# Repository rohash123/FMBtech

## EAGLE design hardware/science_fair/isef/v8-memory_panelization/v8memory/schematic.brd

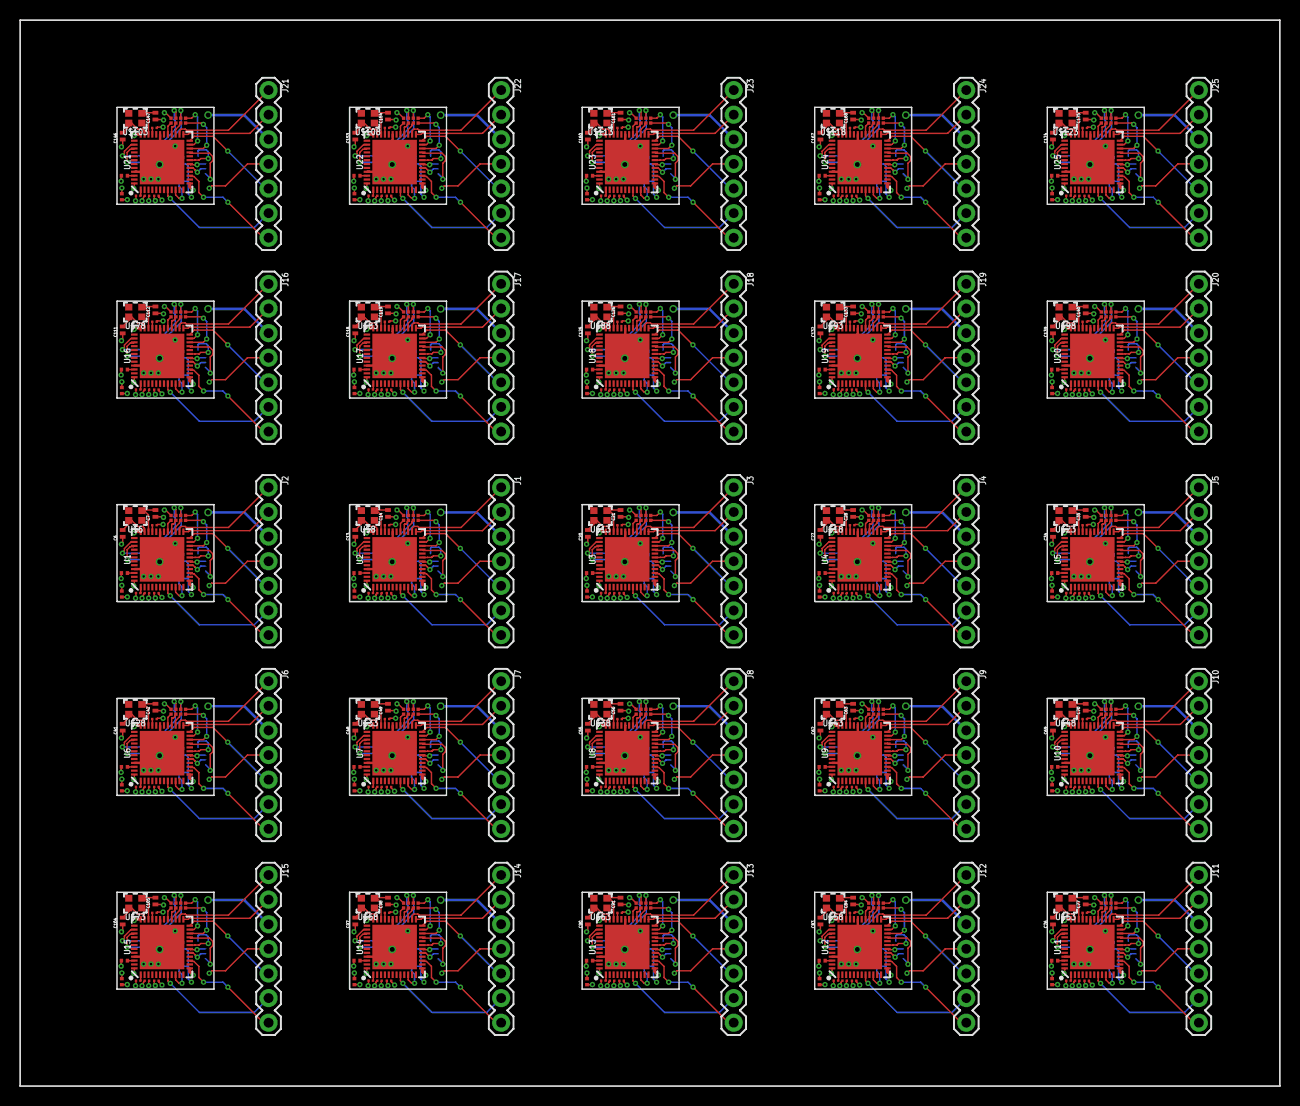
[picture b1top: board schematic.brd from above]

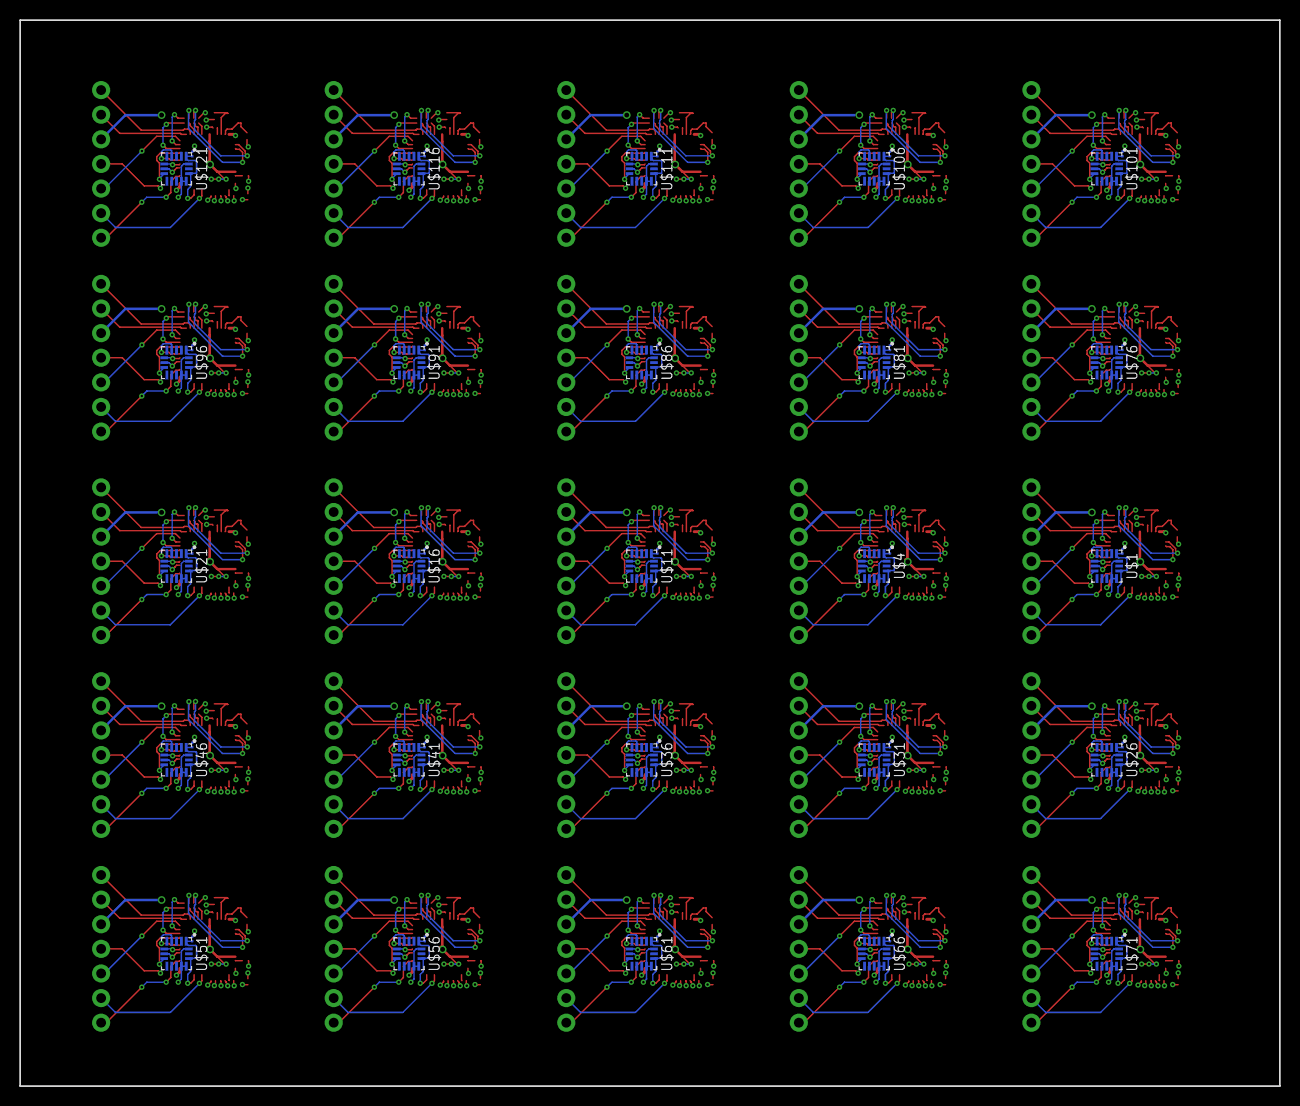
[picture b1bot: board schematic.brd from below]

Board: 4 copper layers, 130.0 x 110.0 mm, 350 parts (50 on the bottom side), 600 nets.

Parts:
C1, C2, C3, C4, C8, C9, C10, C11, C15, C16, C17, C18, C22, C23, C24, C25, C29, C30, C31, C32, C36, C37, C38, C39, C43, C44, C45, C46, C50, C51, C52, C53, C57, C58, C59, C60, C64, C65, C66, C67, C71, C72, C73, C74, C78, C79, C80, C81, C85, C86, C87, C88, C92, C93, C94, C95, C99, C100, C101, C102, C106, C107, C108, C109, C113, C114, C115, C116, C120, C121, C122, C123, C127, C128, C129, C130, C134, C135, C136, C137, C141, C142, C143, C144, C148, C149, C150, C151, C155, C156, C157, C158, C162, C163, C164, C165, C169, C170, C171, C172: C0402X5R0G104M020BCCAP_0402-L; CAP_0402-L
C5, C12, C19, C26, C33, C40, C47, C54, C61, C68, C75, C82, C89, C96, C103, C110, C117, C124, C131, C138, C145, C152, C159, C166, C173: C0402C0G1C101J020BCCAP_0402-L; CAP_0402-L
C6, C7, C13, C14, C20, C21, C27, C28, C34, C35, C41, C42, C48, C49, C55, C56, C62, C63, C69, C70, C76, C77, C83, C84, C90, C91, C97, C98, C104, C105, C111, C112, C118, C119, C125, C126, C132, C133, C139, C140, C146, C147, C153, C154, C160, C161, C167, C168, C174, C175: GRM1555C1H6R0CA01D; CAPC1005X55N
J1, J2, J3, J4, J5, J6, J7, J8, J9, J10, J11, J12, J13, J14, J15, J16, J17, J18, J19, J20, J21, J22, J23, J24, J25: header; 1X07
U1, U2, U3, U4, U5, U6, U7, U8, U9, U10, U11, U12, U13, U14, U15, U16, U17, U18, U19, U20, U21, U22, U23, U24, U25: NRF52832; QFN48-6X6MM
U$1, U$4, U$11, U$16, U$21, U$26, U$31, U$36, U$41, U$46, U$51, U$56, U$61, U$66, U$71, U$76, U$81, U$86, U$91, U$96, U$101, U$106, U$111, U$116, U$121: ADXL362; TFLGA-16/3.3MMX3.1MM
U$2, U$5, U$12, U$17, U$22, U$27, U$32, U$37, U$42, U$47, U$52, U$57, U$62, U$67, U$72, U$77, U$82, U$87, U$92, U$97, U$102, U$107, U$112, U$117, U$122: 4P7UFCAPACITOR
U$3, U$10, U$15, U$20, U$25, U$30, U$35, U$40, U$45, U$50, U$55, U$60, U$65, U$70, U$75, U$80, U$85, U$90, U$95, U$100, U$105, U$110, U$115, U$120, U$125: AT25SF161-UUD-T
U$6, U$8, U$13, U$18, U$23, U$28, U$33, U$38, U$43, U$48, U$53, U$58, U$63, U$68, U$73, U$78, U$83, U$88, U$93, U$98, U$103, U$108, U$113, U$118, U$123: 32MHZCRYSTAL
U$7, U$9, U$14, U$19, U$24, U$29, U$34, U$39, U$44, U$49, U$54, U$59, U$64, U$69, U$74, U$79, U$84, U$89, U$94, U$99, U$104, U$109, U$114, U$119, U$124: 1UFCAPACITOR

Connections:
ADXL_POWER-QFAA: C1.2, U1.10, U$1.VDD/IO, U$1.VS
ADXL_POWER-QFAA1: C8.2, U2.10, U$4.VDD/IO, U$4.VS
ADXL_POWER-QFAA2: C15.2, U3.10, U$11.VDD/IO, U$11.VS
ADXL_POWER-QFAA3: C22.2, U4.10, U$16.VDD/IO, U$16.VS
ADXL_POWER-QFAA4: C29.2, U5.10, U$21.VDD/IO, U$21.VS
ADXL_POWER-QFAA5: C36.2, U6.10, U$26.VDD/IO, U$26.VS
ADXL_POWER-QFAA6: C43.2, U7.10, U$31.VDD/IO, U$31.VS
ADXL_POWER-QFAA7: C50.2, U8.10, U$36.VDD/IO, U$36.VS
ADXL_POWER-QFAA8: C57.2, U9.10, U$41.VDD/IO, U$41.VS
ADXL_POWER-QFAA9: C64.2, U10.10, U$46.VDD/IO, U$46.VS
ADXL_POWER-QFAA10: C71.2, U11.10, U$51.VDD/IO, U$51.VS
ADXL_POWER-QFAA11: C78.2, U12.10, U$56.VDD/IO, U$56.VS
ADXL_POWER-QFAA12: C85.2, U13.10, U$61.VDD/IO, U$61.VS
ADXL_POWER-QFAA13: C92.2, U14.10, U$66.VDD/IO, U$66.VS
ADXL_POWER-QFAA14: C99.2, U15.10, U$71.VDD/IO, U$71.VS
ADXL_POWER-QFAA15: C106.2, U16.10, U$76.VDD/IO, U$76.VS
ADXL_POWER-QFAA16: C113.2, U17.10, U$81.VDD/IO, U$81.VS
ADXL_POWER-QFAA17: C120.2, U18.10, U$86.VDD/IO, U$86.VS
ADXL_POWER-QFAA18: C127.2, U19.10, U$91.VDD/IO, U$91.VS
ADXL_POWER-QFAA19: C134.2, U20.10, U$96.VDD/IO, U$96.VS
ADXL_POWER-QFAA20: C141.2, U21.10, U$101.VDD/IO, U$101.VS
ADXL_POWER-QFAA21: C148.2, U22.10, U$106.VDD/IO, U$106.VS
ADXL_POWER-QFAA22: C155.2, U23.10, U$111.VDD/IO, U$111.VS
ADXL_POWER-QFAA23: C162.2, U24.10, U$116.VDD/IO, U$116.VS
ADXL_POWER-QFAA24: C169.2, U25.10, U$121.VDD/IO, U$121.VS
CS-QFAA: U1.21, U$1.CS
CS-QFAA1: U2.21, U$4.CS
CS-QFAA2: U3.21, U$11.CS
CS-QFAA3: U4.21, U$16.CS
CS-QFAA4: U5.21, U$21.CS
CS-QFAA5: U6.21, U$26.CS
CS-QFAA6: U7.21, U$31.CS
CS-QFAA7: U8.21, U$36.CS
CS-QFAA8: U9.21, U$41.CS
CS-QFAA9: U10.21, U$46.CS
CS-QFAA10: U11.21, U$51.CS
CS-QFAA11: U12.21, U$56.CS
CS-QFAA12: U13.21, U$61.CS
CS-QFAA13: U14.21, U$66.CS
CS-QFAA14: U15.21, U$71.CS
CS-QFAA15: U16.21, U$76.CS
CS-QFAA16: U17.21, U$81.CS
CS-QFAA17: U18.21, U$86.CS
CS-QFAA18: U19.21, U$91.CS
CS-QFAA19: U20.21, U$96.CS
CS-QFAA20: U21.21, U$101.CS
CS-QFAA21: U22.21, U$106.CS
CS-QFAA22: U23.21, U$111.CS
CS-QFAA23: U24.21, U$116.CS
CS-QFAA24: U25.21, U$121.CS
CS_FLASH: U1.23, U$3.5
CS_FLASH1: U2.23, U$10.5
CS_FLASH2: U3.23, U$15.5
CS_FLASH3: U4.23, U$20.5
CS_FLASH4: U5.23, U$25.5
CS_FLASH5: U6.23, U$30.5
CS_FLASH6: U7.23, U$35.5
CS_FLASH7: U8.23, U$40.5
CS_FLASH8: U9.23, U$45.5
CS_FLASH9: U10.23, U$50.5
CS_FLASH10: U11.23, U$55.5
CS_FLASH11: U12.23, U$60.5
CS_FLASH12: U13.23, U$65.5
CS_FLASH13: U14.23, U$70.5
CS_FLASH14: U15.23, U$75.5
CS_FLASH15: U16.23, U$80.5
CS_FLASH16: U17.23, U$85.5
CS_FLASH17: U18.23, U$90.5
CS_FLASH18: U19.23, U$95.5
CS_FLASH19: U20.23, U$100.5
CS_FLASH20: U21.23, U$105.5
CS_FLASH21: U22.23, U$110.5
CS_FLASH22: U23.23, U$115.5
CS_FLASH23: U24.23, U$120.5
CS_FLASH24: U25.23, U$125.5
DEC1-QFAA: C2.1, U1.1
DEC1-QFAA1: C9.1, U2.1
DEC1-QFAA2: C16.1, U3.1
DEC1-QFAA3: C23.1, U4.1
DEC1-QFAA4: C30.1, U5.1
DEC1-QFAA5: C37.1, U6.1
DEC1-QFAA6: C44.1, U7.1
DEC1-QFAA7: C51.1, U8.1
DEC1-QFAA8: C58.1, U9.1
DEC1-QFAA9: C65.1, U10.1
DEC1-QFAA10: C72.1, U11.1
DEC1-QFAA11: C79.1, U12.1
DEC1-QFAA12: C86.1, U13.1
DEC1-QFAA13: C93.1, U14.1
DEC1-QFAA14: C100.1, U15.1
DEC1-QFAA15: C107.1, U16.1
DEC1-QFAA16: C114.1, U17.1
DEC1-QFAA17: C121.1, U18.1
DEC1-QFAA18: C128.1, U19.1
DEC1-QFAA19: C135.1, U20.1
DEC1-QFAA20: C142.1, U21.1
DEC1-QFAA21: C149.1, U22.1
DEC1-QFAA22: C156.1, U23.1
DEC1-QFAA23: C163.1, U24.1
DEC1-QFAA24: C170.1, U25.1
DEC3-QFAA: C5.1, U1.33
DEC3-QFAA1: C12.1, U2.33
DEC3-QFAA2: C19.1, U3.33
DEC3-QFAA3: C26.1, U4.33
DEC3-QFAA4: C33.1, U5.33
DEC3-QFAA5: C40.1, U6.33
DEC3-QFAA6: C47.1, U7.33
DEC3-QFAA7: C54.1, U8.33
DEC3-QFAA8: C61.1, U9.33
DEC3-QFAA9: C68.1, U10.33
DEC3-QFAA10: C75.1, U11.33
DEC3-QFAA11: C82.1, U12.33
DEC3-QFAA12: C89.1, U13.33
DEC3-QFAA13: C96.1, U14.33
DEC3-QFAA14: C103.1, U15.33
DEC3-QFAA15: C110.1, U16.33
DEC3-QFAA16: C117.1, U17.33
DEC3-QFAA17: C124.1, U18.33
DEC3-QFAA18: C131.1, U19.33
DEC3-QFAA19: C138.1, U20.33
DEC3-QFAA20: C145.1, U21.33
DEC3-QFAA21: C152.1, U22.33
DEC3-QFAA22: C159.1, U23.33
DEC3-QFAA23: C166.1, U24.33
DEC3-QFAA24: C173.1, U25.33
DEC4-QFAA: U1.46, U$7.P$4
DEC4-QFAA1: U2.46, U$9.P$4
DEC4-QFAA2: U3.46, U$14.P$4
DEC4-QFAA3: U4.46, U$19.P$4
DEC4-QFAA4: U5.46, U$24.P$4
DEC4-QFAA5: U6.46, U$29.P$4
DEC4-QFAA6: U7.46, U$34.P$4
DEC4-QFAA7: U8.46, U$39.P$4
DEC4-QFAA8: U9.46, U$44.P$4
DEC4-QFAA9: U10.46, U$49.P$4
DEC4-QFAA10: U11.46, U$54.P$4
DEC4-QFAA11: U12.46, U$59.P$4
DEC4-QFAA12: U13.46, U$64.P$4
DEC4-QFAA13: U14.46, U$69.P$4
DEC4-QFAA14: U15.46, U$74.P$4
DEC4-QFAA15: U16.46, U$79.P$4
DEC4-QFAA16: U17.46, U$84.P$4
DEC4-QFAA17: U18.46, U$89.P$4
DEC4-QFAA18: U19.46, U$94.P$4
DEC4-QFAA19: U20.46, U$99.P$4
DEC4-QFAA20: U21.46, U$104.P$4
DEC4-QFAA21: U22.46, U$109.P$4
DEC4-QFAA22: U23.46, U$114.P$4
DEC4-QFAA23: U24.46, U$119.P$4
DEC4-QFAA24: U25.46, U$124.P$4
FLASH_POWER: U1.22, U$3.1
FLASH_POWER1: U2.22, U$10.1
FLASH_POWER2: U3.22, U$15.1
FLASH_POWER3: U4.22, U$20.1
FLASH_POWER4: U5.22, U$25.1
FLASH_POWER5: U6.22, U$30.1
FLASH_POWER6: U7.22, U$35.1
FLASH_POWER7: U8.22, U$40.1
FLASH_POWER8: U9.22, U$45.1
FLASH_POWER9: U10.22, U$50.1
FLASH_POWER10: U11.22, U$55.1
FLASH_POWER11: U12.22, U$60.1
FLASH_POWER12: U13.22, U$65.1
FLASH_POWER13: U14.22, U$70.1
FLASH_POWER14: U15.22, U$75.1
FLASH_POWER15: U16.22, U$80.1
FLASH_POWER16: U17.22, U$85.1
FLASH_POWER17: U18.22, U$90.1
FLASH_POWER18: U19.22, U$95.1
FLASH_POWER19: U20.22, U$100.1
FLASH_POWER20: U21.22, U$105.1
FLASH_POWER21: U22.22, U$110.1
FLASH_POWER22: U23.22, U$115.1
FLASH_POWER23: U24.22, U$120.1
FLASH_POWER24: U25.22, U$125.1
GND: C1.1, C2.2, C3.1, C4.1, C5.2, C6.1, C7.1, J2.4, U1.31, U1.45, U1.EP, U$1.GND@1, U$1.GND@2, U$1.GND@3, U$2.P$4, U$3.8, U$7.P$3
GND1: C8.1, C9.2, C10.1, C11.1, C12.2, C13.1, C14.1, J1.4, U2.31, U2.45, U2.EP, U$4.GND@1, U$4.GND@2, U$4.GND@3, U$5.P$4, U$9.P$3, U$10.8
GND2: C15.1, C16.2, C17.1, C18.1, C19.2, C20.1, C21.1, J3.4, U3.31, U3.45, U3.EP, U$11.GND@1, U$11.GND@2, U$11.GND@3, U$12.P$4, U$14.P$3, U$15.8
GND3: C22.1, C23.2, C24.1, C25.1, C26.2, C27.1, C28.1, J4.4, U4.31, U4.45, U4.EP, U$16.GND@1, U$16.GND@2, U$16.GND@3, U$17.P$4, U$19.P$3, U$20.8
GND4: C29.1, C30.2, C31.1, C32.1, C33.2, C34.1, C35.1, J5.4, U5.31, U5.45, U5.EP, U$21.GND@1, U$21.GND@2, U$21.GND@3, U$22.P$4, U$24.P$3, U$25.8
GND5: C36.1, C37.2, C38.1, C39.1, C40.2, C41.1, C42.1, J6.4, U6.31, U6.45, U6.EP, U$26.GND@1, U$26.GND@2, U$26.GND@3, U$27.P$4, U$29.P$3, U$30.8
GND6: C43.1, C44.2, C45.1, C46.1, C47.2, C48.1, C49.1, J7.4, U7.31, U7.45, U7.EP, U$31.GND@1, U$31.GND@2, U$31.GND@3, U$32.P$4, U$34.P$3, U$35.8
GND7: C50.1, C51.2, C52.1, C53.1, C54.2, C55.1, C56.1, J8.4, U8.31, U8.45, U8.EP, U$36.GND@1, U$36.GND@2, U$36.GND@3, U$37.P$4, U$39.P$3, U$40.8
GND8: C57.1, C58.2, C59.1, C60.1, C61.2, C62.1, C63.1, J9.4, U9.31, U9.45, U9.EP, U$41.GND@1, U$41.GND@2, U$41.GND@3, U$42.P$4, U$44.P$3, U$45.8
GND9: C64.1, C65.2, C66.1, C67.1, C68.2, C69.1, C70.1, J10.4, U10.31, U10.45, U10.EP, U$46.GND@1, U$46.GND@2, U$46.GND@3, U$47.P$4, U$49.P$3, U$50.8
GND10: C71.1, C72.2, C73.1, C74.1, C75.2, C76.1, C77.1, J11.4, U11.31, U11.45, U11.EP, U$51.GND@1, U$51.GND@2, U$51.GND@3, U$52.P$4, U$54.P$3, U$55.8
GND11: C78.1, C79.2, C80.1, C81.1, C82.2, C83.1, C84.1, J12.4, U12.31, U12.45, U12.EP, U$56.GND@1, U$56.GND@2, U$56.GND@3, U$57.P$4, U$59.P$3, U$60.8
GND12: C85.1, C86.2, C87.1, C88.1, C89.2, C90.1, C91.1, J13.4, U13.31, U13.45, U13.EP, U$61.GND@1, U$61.GND@2, U$61.GND@3, U$62.P$4, U$64.P$3, U$65.8
GND13: C92.1, C93.2, C94.1, C95.1, C96.2, C97.1, C98.1, J14.4, U14.31, U14.45, U14.EP, U$66.GND@1, U$66.GND@2, U$66.GND@3, U$67.P$4, U$69.P$3, U$70.8
GND14: C99.1, C100.2, C101.1, C102.1, C103.2, C104.1, C105.1, J15.4, U15.31, U15.45, U15.EP, U$71.GND@1, U$71.GND@2, U$71.GND@3, U$72.P$4, U$74.P$3, U$75.8
GND15: C106.1, C107.2, C108.1, C109.1, C110.2, C111.1, C112.1, J16.4, U16.31, U16.45, U16.EP, U$76.GND@1, U$76.GND@2, U$76.GND@3, U$77.P$4, U$79.P$3, U$80.8
GND16: C113.1, C114.2, C115.1, C116.1, C117.2, C118.1, C119.1, J17.4, U17.31, U17.45, U17.EP, U$81.GND@1, U$81.GND@2, U$81.GND@3, U$82.P$4, U$84.P$3, U$85.8
GND17: C120.1, C121.2, C122.1, C123.1, C124.2, C125.1, C126.1, J18.4, U18.31, U18.45, U18.EP, U$86.GND@1, U$86.GND@2, U$86.GND@3, U$87.P$4, U$89.P$3, U$90.8
GND18: C127.1, C128.2, C129.1, C130.1, C131.2, C132.1, C133.1, J19.4, U19.31, U19.45, U19.EP, U$91.GND@1, U$91.GND@2, U$91.GND@3, U$92.P$4, U$94.P$3, U$95.8
GND19: C134.1, C135.2, C136.1, C137.1, C138.2, C139.1, C140.1, J20.4, U20.31, U20.45, U20.EP, U$96.GND@1, U$96.GND@2, U$96.GND@3, U$97.P$4, U$99.P$3, U$100.8
GND20: C141.1, C142.2, C143.1, C144.1, C145.2, C146.1, C147.1, J21.4, U21.31, U21.45, U21.EP, U$101.GND@1, U$101.GND@2, U$101.GND@3, U$102.P$4, U$104.P$3, U$105.8
GND21: C148.1, C149.2, C150.1, C151.1, C152.2, C153.1, C154.1, J22.4, U22.31, U22.45, U22.EP, U$106.GND@1, U$106.GND@2, U$106.GND@3, U$107.P$4, U$109.P$3, U$110.8
GND22: C155.1, C156.2, C157.1, C158.1, C159.2, C160.1, C161.1, J23.4, U23.31, U23.45, U23.EP, U$111.GND@1, U$111.GND@2, U$111.GND@3, U$112.P$4, U$114.P$3, U$115.8
GND23: C162.1, C163.2, C164.1, C165.1, C166.2, C167.1, C168.1, J24.4, U24.31, U24.45, U24.EP, U$116.GND@1, U$116.GND@2, U$116.GND@3, U$117.P$4, U$119.P$3, U$120.8
GND24: C169.1, C170.2, C171.1, C172.1, C173.2, C174.1, C175.1, J25.4, U25.31, U25.45, U25.EP, U$121.GND@1, U$121.GND@2, U$121.GND@3, U$122.P$4, U$124.P$3, U$125.8
HOLD_FLASH: U1.27, U$3.2
HOLD_FLASH1: U2.27, U$10.2
HOLD_FLASH2: U3.27, U$15.2
HOLD_FLASH3: U4.27, U$20.2
HOLD_FLASH4: U5.27, U$25.2
HOLD_FLASH5: U6.27, U$30.2
HOLD_FLASH6: U7.27, U$35.2
HOLD_FLASH7: U8.27, U$40.2
HOLD_FLASH8: U9.27, U$45.2
HOLD_FLASH9: U10.27, U$50.2
HOLD_FLASH10: U11.27, U$55.2
HOLD_FLASH11: U12.27, U$60.2
HOLD_FLASH12: U13.27, U$65.2
HOLD_FLASH13: U14.27, U$70.2
HOLD_FLASH14: U15.27, U$75.2
HOLD_FLASH15: U16.27, U$80.2
HOLD_FLASH16: U17.27, U$85.2
HOLD_FLASH17: U18.27, U$90.2
HOLD_FLASH18: U19.27, U$95.2
HOLD_FLASH19: U20.27, U$100.2
HOLD_FLASH20: U21.27, U$105.2
HOLD_FLASH21: U22.27, U$110.2
HOLD_FLASH22: U23.27, U$115.2
HOLD_FLASH23: U24.27, U$120.2
HOLD_FLASH24: U25.27, U$125.2
MISO-QFAA: U1.17, U$1.MISO
MISO-QFAA1: U2.17, U$4.MISO
MISO-QFAA2: U3.17, U$11.MISO
MISO-QFAA3: U4.17, U$16.MISO
MISO-QFAA4: U5.17, U$21.MISO
MISO-QFAA5: U6.17, U$26.MISO
MISO-QFAA6: U7.17, U$31.MISO
MISO-QFAA7: U8.17, U$36.MISO
MISO-QFAA8: U9.17, U$41.MISO
MISO-QFAA9: U10.17, U$46.MISO
MISO-QFAA10: U11.17, U$51.MISO
MISO-QFAA11: U12.17, U$56.MISO
MISO-QFAA12: U13.17, U$61.MISO
MISO-QFAA13: U14.17, U$66.MISO
MISO-QFAA14: U15.17, U$71.MISO
MISO-QFAA15: U16.17, U$76.MISO
MISO-QFAA16: U17.17, U$81.MISO
MISO-QFAA17: U18.17, U$86.MISO
MISO-QFAA18: U19.17, U$91.MISO
MISO-QFAA19: U20.17, U$96.MISO
MISO-QFAA20: U21.17, U$101.MISO
MISO-QFAA21: U22.17, U$106.MISO
MISO-QFAA22: U23.17, U$111.MISO
MISO-QFAA23: U24.17, U$116.MISO
MISO-QFAA24: U25.17, U$121.MISO
MOSI-QFAA: U1.18, U$1.MOSI
MOSI-QFAA1: U2.18, U$4.MOSI
MOSI-QFAA2: U3.18, U$11.MOSI
MOSI-QFAA3: U4.18, U$16.MOSI
MOSI-QFAA4: U5.18, U$21.MOSI
MOSI-QFAA5: U6.18, U$26.MOSI
MOSI-QFAA6: U7.18, U$31.MOSI
MOSI-QFAA7: U8.18, U$36.MOSI
MOSI-QFAA8: U9.18, U$41.MOSI
MOSI-QFAA9: U10.18, U$46.MOSI
MOSI-QFAA10: U11.18, U$51.MOSI
MOSI-QFAA11: U12.18, U$56.MOSI
MOSI-QFAA12: U13.18, U$61.MOSI
MOSI-QFAA13: U14.18, U$66.MOSI
MOSI-QFAA14: U15.18, U$71.MOSI
MOSI-QFAA15: U16.18, U$76.MOSI
MOSI-QFAA16: U17.18, U$81.MOSI
MOSI-QFAA17: U18.18, U$86.MOSI
MOSI-QFAA18: U19.18, U$91.MOSI
MOSI-QFAA19: U20.18, U$96.MOSI
MOSI-QFAA20: U21.18, U$101.MOSI
MOSI-QFAA21: U22.18, U$106.MOSI
MOSI-QFAA22: U23.18, U$111.MOSI
MOSI-QFAA23: U24.18, U$116.MOSI
MOSI-QFAA24: U25.18, U$121.MOSI
P0.06-QFAA: J2.6, U1.8
P0.06-QFAA1: J1.6, U2.8
P0.06-QFAA2: J3.6, U3.8
P0.06-QFAA3: J4.6, U4.8
P0.06-QFAA4: J5.6, U5.8
P0.06-QFAA5: J6.6, U6.8
P0.06-QFAA6: J7.6, U7.8
P0.06-QFAA7: J8.6, U8.8
P0.06-QFAA8: J9.6, U9.8
P0.06-QFAA9: J10.6, U10.8
P0.06-QFAA10: J11.6, U11.8
P0.06-QFAA11: J12.6, U12.8
P0.06-QFAA12: J13.6, U13.8
P0.06-QFAA13: J14.6, U14.8
P0.06-QFAA14: J15.6, U15.8
P0.06-QFAA15: J16.6, U16.8
P0.06-QFAA16: J17.6, U17.8
P0.06-QFAA17: J18.6, U18.8
P0.06-QFAA18: J19.6, U19.8
P0.06-QFAA19: J20.6, U20.8
P0.06-QFAA20: J21.6, U21.8
P0.06-QFAA21: J22.6, U22.8
P0.06-QFAA22: J23.6, U23.8
P0.06-QFAA23: J24.6, U24.8
P0.06-QFAA24: J25.6, U25.8
P0.12-QFAA: J2.7, U1.15
P0.12-QFAA1: J1.7, U2.15
P0.12-QFAA2: J3.7, U3.15
P0.12-QFAA3: J4.7, U4.15
P0.12-QFAA4: J5.7, U5.15
P0.12-QFAA5: J6.7, U6.15
P0.12-QFAA6: J7.7, U7.15
P0.12-QFAA7: J8.7, U8.15
P0.12-QFAA8: J9.7, U9.15
P0.12-QFAA9: J10.7, U10.15
P0.12-QFAA10: J11.7, U11.15
P0.12-QFAA11: J12.7, U12.15
P0.12-QFAA12: J13.7, U13.15
P0.12-QFAA13: J14.7, U14.15
P0.12-QFAA14: J15.7, U15.15
P0.12-QFAA15: J16.7, U16.15
P0.12-QFAA16: J17.7, U17.15
P0.12-QFAA17: J18.7, U18.15
P0.12-QFAA18: J19.7, U19.15
P0.12-QFAA19: J20.7, U20.15
P0.12-QFAA20: J21.7, U21.15
P0.12-QFAA21: J22.7, U22.15
P0.12-QFAA22: J23.7, U23.15
P0.12-QFAA23: J24.7, U24.15
P0.12-QFAA24: J25.7, U25.15
RESET-QFAA: J2.5, U1.24
RESET-QFAA1: J1.5, U2.24
RESET-QFAA2: J3.5, U3.24
RESET-QFAA3: J4.5, U4.24
RESET-QFAA4: J5.5, U5.24
RESET-QFAA5: J6.5, U6.24
RESET-QFAA6: J7.5, U7.24
RESET-QFAA7: J8.5, U8.24
RESET-QFAA8: J9.5, U9.24
RESET-QFAA9: J10.5, U10.24
RESET-QFAA10: J11.5, U11.24
RESET-QFAA11: J12.5, U12.24
RESET-QFAA12: J13.5, U13.24
RESET-QFAA13: J14.5, U14.24
RESET-QFAA14: J15.5, U15.24
RESET-QFAA15: J16.5, U16.24
RESET-QFAA16: J17.5, U17.24
RESET-QFAA17: J18.5, U18.24
RESET-QFAA18: J19.5, U19.24
RESET-QFAA19: J20.5, U20.24
RESET-QFAA20: J21.5, U21.24
RESET-QFAA21: J22.5, U22.24
RESET-QFAA22: J23.5, U23.24
RESET-QFAA23: J24.5, U24.24
RESET-QFAA24: J25.5, U25.24
SCK_FLASH: U1.28, U$3.3
SCK_FLASH1: U2.28, U$10.3
SCK_FLASH2: U3.28, U$15.3
SCK_FLASH3: U4.28, U$20.3
SCK_FLASH4: U5.28, U$25.3
SCK_FLASH5: U6.28, U$30.3
SCK_FLASH6: U7.28, U$35.3
SCK_FLASH7: U8.28, U$40.3
SCK_FLASH8: U9.28, U$45.3
SCK_FLASH9: U10.28, U$50.3
SCK_FLASH10: U11.28, U$55.3
SCK_FLASH11: U12.28, U$60.3
SCK_FLASH12: U13.28, U$65.3
SCK_FLASH13: U14.28, U$70.3
SCK_FLASH14: U15.28, U$75.3
SCK_FLASH15: U16.28, U$80.3
SCK_FLASH16: U17.28, U$85.3
SCK_FLASH17: U18.28, U$90.3
SCK_FLASH18: U19.28, U$95.3
SCK_FLASH19: U20.28, U$100.3
SCK_FLASH20: U21.28, U$105.3
SCK_FLASH21: U22.28, U$110.3
SCK_FLASH22: U23.28, U$115.3
SCK_FLASH23: U24.28, U$120.3
SCK_FLASH24: U25.28, U$125.3
SCLK-QFAA: U1.19, U$1.SCLK
SCLK-QFAA1: U2.19, U$4.SCLK
SCLK-QFAA2: U3.19, U$11.SCLK
SCLK-QFAA3: U4.19, U$16.SCLK
SCLK-QFAA4: U5.19, U$21.SCLK
SCLK-QFAA5: U6.19, U$26.SCLK
SCLK-QFAA6: U7.19, U$31.SCLK
SCLK-QFAA7: U8.19, U$36.SCLK
SCLK-QFAA8: U9.19, U$41.SCLK
SCLK-QFAA9: U10.19, U$46.SCLK
SCLK-QFAA10: U11.19, U$51.SCLK
SCLK-QFAA11: U12.19, U$56.SCLK
SCLK-QFAA12: U13.19, U$61.SCLK
SCLK-QFAA13: U14.19, U$66.SCLK
SCLK-QFAA14: U15.19, U$71.SCLK
SCLK-QFAA15: U16.19, U$76.SCLK
SCLK-QFAA16: U17.19, U$81.SCLK
SCLK-QFAA17: U18.19, U$86.SCLK
SCLK-QFAA18: U19.19, U$91.SCLK
SCLK-QFAA19: U20.19, U$96.SCLK
SCLK-QFAA20: U21.19, U$101.SCLK
SCLK-QFAA21: U22.19, U$106.SCLK
SCLK-QFAA22: U23.19, U$111.SCLK
SCLK-QFAA23: U24.19, U$116.SCLK
SCLK-QFAA24: U25.19, U$121.SCLK
SI_FLASH: U1.29, U$3.4
SI_FLASH1: U2.29, U$10.4
SI_FLASH2: U3.29, U$15.4
SI_FLASH3: U4.29, U$20.4
SI_FLASH4: U5.29, U$25.4
SI_FLASH5: U6.29, U$30.4
SI_FLASH6: U7.29, U$35.4
SI_FLASH7: U8.29, U$40.4
SI_FLASH8: U9.29, U$45.4
SI_FLASH9: U10.29, U$50.4
SI_FLASH10: U11.29, U$55.4
SI_FLASH11: U12.29, U$60.4
SI_FLASH12: U13.29, U$65.4
SI_FLASH13: U14.29, U$70.4
SI_FLASH14: U15.29, U$75.4
SI_FLASH15: U16.29, U$80.4
SI_FLASH16: U17.29, U$85.4
SI_FLASH17: U18.29, U$90.4
SI_FLASH18: U19.29, U$95.4
SI_FLASH19: U20.29, U$100.4
SI_FLASH20: U21.29, U$105.4
SI_FLASH21: U22.29, U$110.4
SI_FLASH22: U23.29, U$115.4
SI_FLASH23: U24.29, U$120.4
SI_FLASH24: U25.29, U$125.4
SO_FLASH: U1.39, U$3.6
SO_FLASH1: U2.39, U$10.6
SO_FLASH2: U3.39, U$15.6
SO_FLASH3: U4.39, U$20.6
SO_FLASH4: U5.39, U$25.6
SO_FLASH5: U6.39, U$30.6
SO_FLASH6: U7.39, U$35.6
SO_FLASH7: U8.39, U$40.6
SO_FLASH8: U9.39, U$45.6
SO_FLASH9: U10.39, U$50.6
SO_FLASH10: U11.39, U$55.6
SO_FLASH11: U12.39, U$60.6
SO_FLASH12: U13.39, U$65.6
SO_FLASH13: U14.39, U$70.6
SO_FLASH14: U15.39, U$75.6
SO_FLASH15: U16.39, U$80.6
SO_FLASH16: U17.39, U$85.6
SO_FLASH17: U18.39, U$90.6
SO_FLASH18: U19.39, U$95.6
SO_FLASH19: U20.39, U$100.6
SO_FLASH20: U21.39, U$105.6
SO_FLASH21: U22.39, U$110.6
SO_FLASH22: U23.39, U$115.6
SO_FLASH23: U24.39, U$120.6
SO_FLASH24: U25.39, U$125.6
SWDCLK-QFAA: J2.2, U1.25
SWDCLK-QFAA1: J1.2, U2.25
SWDCLK-QFAA2: J3.2, U3.25
SWDCLK-QFAA3: J4.2, U4.25
SWDCLK-QFAA4: J5.2, U5.25
SWDCLK-QFAA5: J6.2, U6.25
SWDCLK-QFAA6: J7.2, U7.25
SWDCLK-QFAA7: J8.2, U8.25
SWDCLK-QFAA8: J9.2, U9.25
SWDCLK-QFAA9: J10.2, U10.25
SWDCLK-QFAA10: J11.2, U11.25
SWDCLK-QFAA11: J12.2, U12.25
SWDCLK-QFAA12: J13.2, U13.25
SWDCLK-QFAA13: J14.2, U14.25
SWDCLK-QFAA14: J15.2, U15.25
SWDCLK-QFAA15: J16.2, U16.25
SWDCLK-QFAA16: J17.2, U17.25
SWDCLK-QFAA17: J18.2, U18.25
SWDCLK-QFAA18: J19.2, U19.25
SWDCLK-QFAA19: J20.2, U20.25
SWDCLK-QFAA20: J21.2, U21.25
SWDCLK-QFAA21: J22.2, U22.25
SWDCLK-QFAA22: J23.2, U23.25
SWDCLK-QFAA23: J24.2, U24.25
SWDCLK-QFAA24: J25.2, U25.25
SWDIO-QFAA: J2.1, U1.26
SWDIO-QFAA1: J1.1, U2.26
SWDIO-QFAA2: J3.1, U3.26
SWDIO-QFAA3: J4.1, U4.26
SWDIO-QFAA4: J5.1, U5.26
SWDIO-QFAA5: J6.1, U6.26
SWDIO-QFAA6: J7.1, U7.26
SWDIO-QFAA7: J8.1, U8.26
SWDIO-QFAA8: J9.1, U9.26
SWDIO-QFAA9: J10.1, U10.26
SWDIO-QFAA10: J11.1, U11.26
SWDIO-QFAA11: J12.1, U12.26
SWDIO-QFAA12: J13.1, U13.26
SWDIO-QFAA13: J14.1, U14.26
SWDIO-QFAA14: J15.1, U15.26
SWDIO-QFAA15: J16.1, U16.26
SWDIO-QFAA16: J17.1, U17.26
SWDIO-QFAA17: J18.1, U18.26
SWDIO-QFAA18: J19.1, U19.26
SWDIO-QFAA19: J20.1, U20.26
SWDIO-QFAA20: J21.1, U21.26
SWDIO-QFAA21: J22.1, U22.26
SWDIO-QFAA22: J23.1, U23.26
SWDIO-QFAA23: J24.1, U24.26
SWDIO-QFAA24: J25.1, U25.26
VDD: C3.2, C4.2, J2.3, U1.13, U1.36, U1.48, U$2.P$3
VDD1: C10.2, C11.2, J1.3, U2.13, U2.36, U2.48, U$5.P$3
VDD2: C17.2, C18.2, J3.3, U3.13, U3.36, U3.48, U$12.P$3
VDD3: C24.2, C25.2, J4.3, U4.13, U4.36, U4.48, U$17.P$3
VDD4: C31.2, C32.2, J5.3, U5.13, U5.36, U5.48, U$22.P$3
VDD5: C38.2, C39.2, J6.3, U6.13, U6.36, U6.48, U$27.P$3
VDD6: C45.2, C46.2, J7.3, U7.13, U7.36, U7.48, U$32.P$3
VDD7: C52.2, C53.2, J8.3, U8.13, U8.36, U8.48, U$37.P$3
VDD8: C59.2, C60.2, J9.3, U9.13, U9.36, U9.48, U$42.P$3
VDD9: C66.2, C67.2, J10.3, U10.13, U10.36, U10.48, U$47.P$3
VDD10: C73.2, C74.2, J11.3, U11.13, U11.36, U11.48, U$52.P$3
VDD11: C80.2, C81.2, J12.3, U12.13, U12.36, U12.48, U$57.P$3
VDD12: C87.2, C88.2, J13.3, U13.13, U13.36, U13.48, U$62.P$3
VDD13: C94.2, C95.2, J14.3, U14.13, U14.36, U14.48, U$67.P$3
VDD14: C101.2, C102.2, J15.3, U15.13, U15.36, U15.48, U$72.P$3
VDD15: C108.2, C109.2, J16.3, U16.13, U16.36, U16.48, U$77.P$3
VDD16: C115.2, C116.2, J17.3, U17.13, U17.36, U17.48, U$82.P$3
VDD17: C122.2, C123.2, J18.3, U18.13, U18.36, U18.48, U$87.P$3
VDD18: C129.2, C130.2, J19.3, U19.13, U19.36, U19.48, U$92.P$3
VDD19: C136.2, C137.2, J20.3, U20.13, U20.36, U20.48, U$97.P$3
VDD20: C143.2, C144.2, J21.3, U21.13, U21.36, U21.48, U$102.P$3
VDD21: C150.2, C151.2, J22.3, U22.13, U22.36, U22.48, U$107.P$3
VDD22: C157.2, C158.2, J23.3, U23.13, U23.36, U23.48, U$112.P$3
VDD23: C164.2, C165.2, J24.3, U24.13, U24.36, U24.48, U$117.P$3
VDD24: C171.2, C172.2, J25.3, U25.13, U25.36, U25.48, U$122.P$3
WP_FLASH: U1.38, U$3.7
WP_FLASH1: U2.38, U$10.7
WP_FLASH2: U3.38, U$15.7
WP_FLASH3: U4.38, U$20.7
WP_FLASH4: U5.38, U$25.7
WP_FLASH5: U6.38, U$30.7
WP_FLASH6: U7.38, U$35.7
WP_FLASH7: U8.38, U$40.7
WP_FLASH8: U9.38, U$45.7
WP_FLASH9: U10.38, U$50.7
WP_FLASH10: U11.38, U$55.7
WP_FLASH11: U12.38, U$60.7
WP_FLASH12: U13.38, U$65.7
WP_FLASH13: U14.38, U$70.7
WP_FLASH14: U15.38, U$75.7
WP_FLASH15: U16.38, U$80.7
WP_FLASH16: U17.38, U$85.7
WP_FLASH17: U18.38, U$90.7
WP_FLASH18: U19.38, U$95.7
WP_FLASH19: U20.38, U$100.7
WP_FLASH20: U21.38, U$105.7
WP_FLASH21: U22.38, U$110.7
WP_FLASH22: U23.38, U$115.7
WP_FLASH23: U24.38, U$120.7
WP_FLASH24: U25.38, U$125.7
XC1-QFAA: C7.2, U1.34, U$6.1
XC1-QFAA1: C14.2, U2.34, U$8.1
XC1-QFAA2: C21.2, U3.34, U$13.1
XC1-QFAA3: C28.2, U4.34, U$18.1
XC1-QFAA4: C35.2, U5.34, U$23.1
XC1-QFAA5: C42.2, U6.34, U$28.1
XC1-QFAA6: C49.2, U7.34, U$33.1
XC1-QFAA7: C56.2, U8.34, U$38.1
XC1-QFAA8: C63.2, U9.34, U$43.1
XC1-QFAA9: C70.2, U10.34, U$48.1
XC1-QFAA10: C77.2, U11.34, U$53.1
XC1-QFAA11: C84.2, U12.34, U$58.1
XC1-QFAA12: C91.2, U13.34, U$63.1
XC1-QFAA13: C98.2, U14.34, U$68.1
XC1-QFAA14: C105.2, U15.34, U$73.1
XC1-QFAA15: C112.2, U16.34, U$78.1
XC1-QFAA16: C119.2, U17.34, U$83.1
XC1-QFAA17: C126.2, U18.34, U$88.1
XC1-QFAA18: C133.2, U19.34, U$93.1
XC1-QFAA19: C140.2, U20.34, U$98.1
XC1-QFAA20: C147.2, U21.34, U$103.1
XC1-QFAA21: C154.2, U22.34, U$108.1
XC1-QFAA22: C161.2, U23.34, U$113.1
XC1-QFAA23: C168.2, U24.34, U$118.1
XC1-QFAA24: C175.2, U25.34, U$123.1
XC2-QFAA: C6.2, U1.35, U$6.3
XC2-QFAA1: C13.2, U2.35, U$8.3
XC2-QFAA2: C20.2, U3.35, U$13.3
XC2-QFAA3: C27.2, U4.35, U$18.3
XC2-QFAA4: C34.2, U5.35, U$23.3
XC2-QFAA5: C41.2, U6.35, U$28.3
XC2-QFAA6: C48.2, U7.35, U$33.3
XC2-QFAA7: C55.2, U8.35, U$38.3
XC2-QFAA8: C62.2, U9.35, U$43.3
XC2-QFAA9: C69.2, U10.35, U$48.3
XC2-QFAA10: C76.2, U11.35, U$53.3
XC2-QFAA11: C83.2, U12.35, U$58.3
XC2-QFAA12: C90.2, U13.35, U$63.3
XC2-QFAA13: C97.2, U14.35, U$68.3
XC2-QFAA14: C104.2, U15.35, U$73.3
XC2-QFAA15: C111.2, U16.35, U$78.3
XC2-QFAA16: C118.2, U17.35, U$83.3
XC2-QFAA17: C125.2, U18.35, U$88.3
XC2-QFAA18: C132.2, U19.35, U$93.3
XC2-QFAA19: C139.2, U20.35, U$98.3
XC2-QFAA20: C146.2, U21.35, U$103.3
XC2-QFAA21: C153.2, U22.35, U$108.3
XC2-QFAA22: C160.2, U23.35, U$113.3
XC2-QFAA23: C167.2, U24.35, U$118.3
XC2-QFAA24: C174.2, U25.35, U$123.3

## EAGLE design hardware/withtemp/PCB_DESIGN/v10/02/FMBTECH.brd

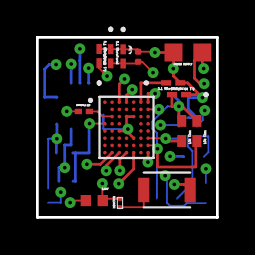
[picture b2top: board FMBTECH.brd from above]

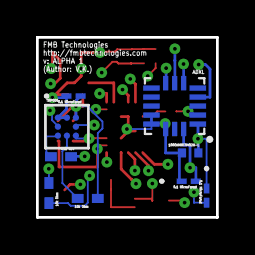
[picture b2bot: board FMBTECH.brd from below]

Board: 6 copper layers, 10.0 x 10.0 mm, 23 parts (9 on the bottom side), 19 nets.

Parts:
ADXL: ADXL362; TFLGA-16/3.3MMX3.1MM
ANT1: ANTENNASMD; 1
C1, C2, C4, C5, C6, C7, C8, C9: 02016D104KAT2A; 0201
C3: GRM0335C1E101JA01D; G-033
NRF: NRF52832-CIAA-R; BGA50N40P7X8_300X320X40
R1, R2, R3, R4, R5: RC0402JR-0710KL; RC0402N
R6: 100OHMRC0402N-L; RES
U1: TMP006BIYZFT; YZF8
U$1: 4.7µF; CAP
U$2: 0.8PF; CAP
U$3: INDUCTOR; 1
U$4: SUPPLY

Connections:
ADXL_POWER: ADXL.1, C9.1, NRF.A3, R6.1
ANT: NRF.D1, U$2.1, U$3.1
CS: ADXL.8, NRF.H5
GND: ADXL.12, ADXL.13, ADXL.16, ANT1.2, C1.2, C2.2, C3.2, C4.1, C5.1, C6.1, C7.1, C8.2, C9.2, NRF.C4, NRF.C5, NRF.E3, NRF.F5, R4.1, R5.1, U1.A1, U1.A2, U$1.1, U$2.2, U$4.P$1
MISO: ADXL.7, NRF.H4
MOSI: ADXL.6, NRF.H3
unnamed: R5.2, U1.C1
unnamed: R4.2, U1.B1
unnamed: R3.1, U1.C2
unnamed: ANT1.1, U$3.2
unnamed: C2.1, NRF.A6
unnamed: C1.1, NRF.B7
unnamed: C3.1, NRF.C2
unnamed: ADXL.14, C8.1, R6.2
SCL: NRF.G7, R2.1, U1.B3
SCLK: ADXL.4, NRF.H2
SDA: NRF.F7, R1.1, U1.C3
TMP_POWER: C4.2, C5.2, NRF.A4, R1.2, R2.2, R3.2, U1.A3
VCC: C6.2, C7.2, NRF.A7, NRF.H7, U$1.2, U$4.P$2

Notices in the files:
parts and their libraries:
SparkFun-Connectors: Licensing: Creative Commons ShareAlike 4.0 International - https://creativecommons.org/licenses/by-sa/4.0
